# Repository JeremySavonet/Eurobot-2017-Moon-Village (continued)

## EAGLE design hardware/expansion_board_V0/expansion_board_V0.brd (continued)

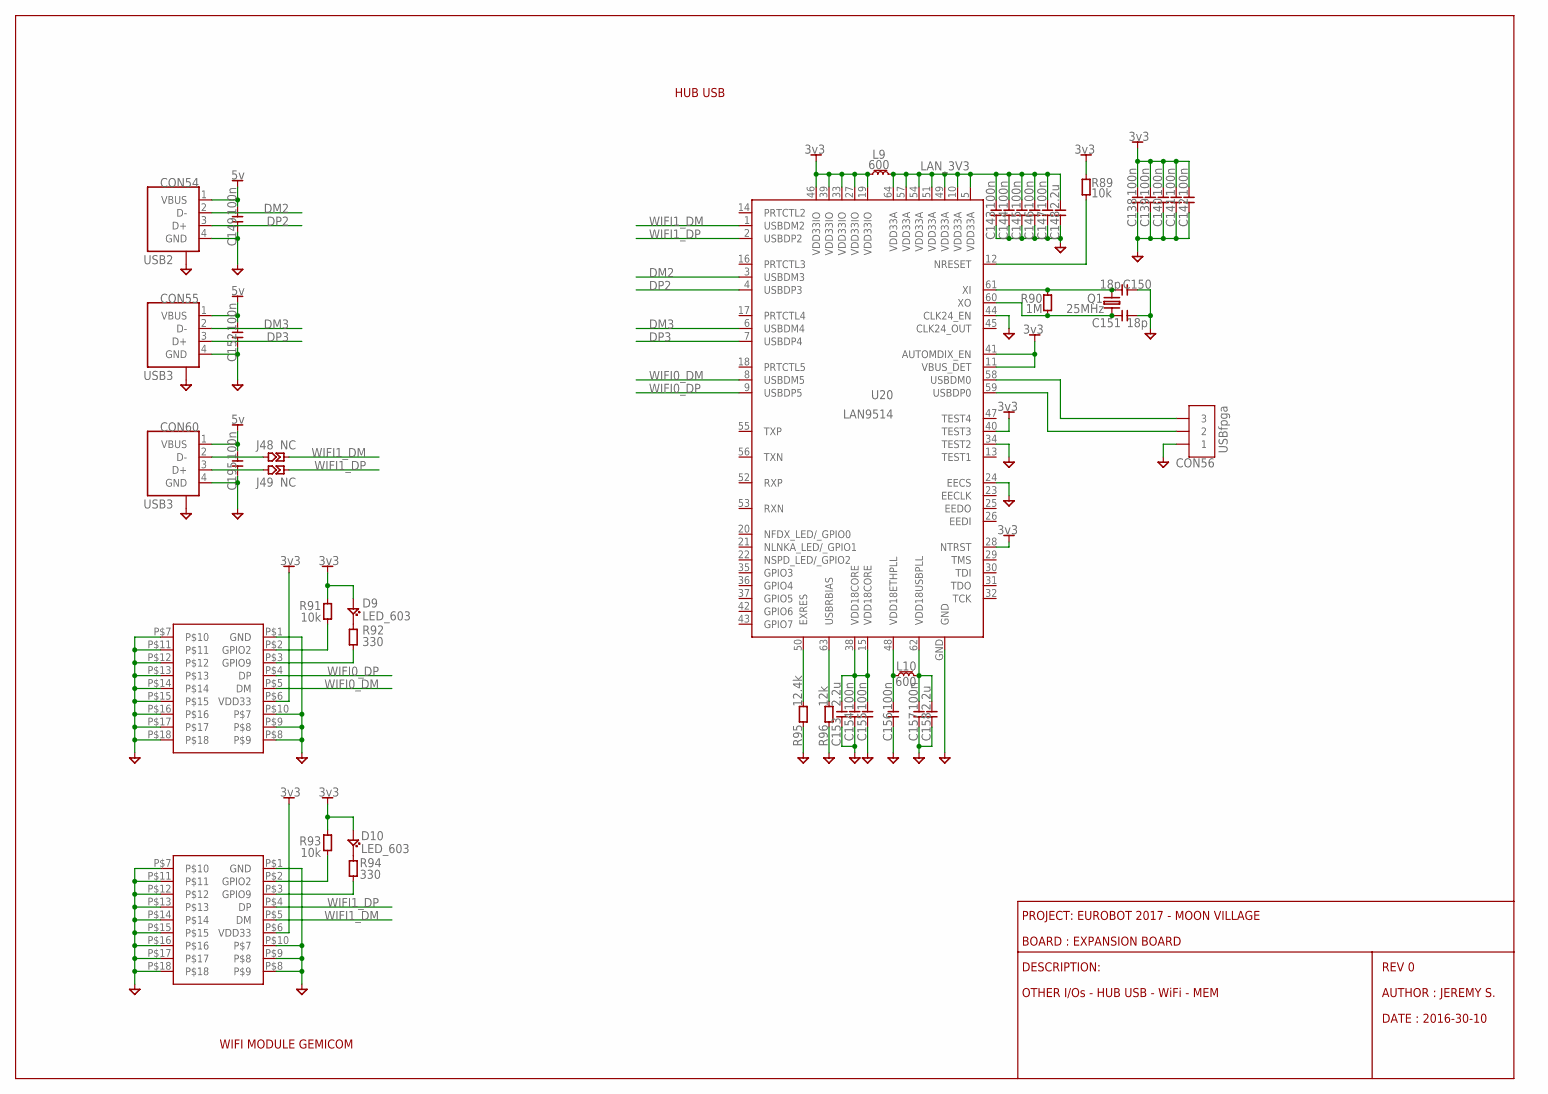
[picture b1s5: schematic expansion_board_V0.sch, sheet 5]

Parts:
C138, C139, C140, C141, C142, C143, C144, C145, C146, C147, C149, C152, C154, C155, C156, C157, C195: 100n; CAPC1005X55N
C148, C153, C158: 2.2u; CAPC1608X95N
C150, C151: 18p; CAPC1005X55N
CON54: USB2; USB_A
CON55, CON60: USB3; USB_A
CON56: USBfpga; CON254P762X400-3N-S
D9, D10: LED_603; LEDC1608X60N
J48, J49: NC; JUMC1005X50N
L9, L10: 600; INDC1608X95N
Q1: 25MHz; XTAL500X320X130N
R89, R91, R93: 10k; RESC1005X40N
R90: 1M; RESC1005X40N
R92, R94: 330; RESC1005X40N
R95: 12.4k; RESC1005X40N
R96: 12k; RESC1005X40N
U20: LAN9514; QFN50P900X900X100-65N
U21, U22: LGA22U

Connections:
3V3: C138.2, C139.2, C140.2, C141.2, C142.2, D9.A, D10.A, L9.1, R89.2, R91.2, R93.2, U20.11 (VBUS_DET), U20.19 (VDD33IO), U20.27 (VDD33IO), U20.28 (NTRST), U20.33 (VDD33IO), U20.39 (VDD33IO), U20.40 (TEST3), U20.41 (AUTOMDIX_EN), U20.46 (VDD33IO), U21.P$6 (VDD33), U22.P$6 (VDD33); also elsewhere on the board
5V: C149.2, C152.2, C195.2, CON54.1 (VBUS), CON55.1 (VBUS), CON60.1 (VBUS); also elsewhere on the board
DM2: CON54.2 (D-), U20.3 (USBDM3)
DM3: CON55.2 (D-), U20.6 (USBDM4)
DP2: CON54.3 (D+), U20.4 (USBDP3)
DP3: CON55.3 (D+), U20.7 (USBDP4)
GND: C138.1, C139.1, C140.1, C141.1, C142.1, C143.1, C144.1, C145.1, C146.1, C147.1, C148.P$1, C149.1, C150.1, C151.1, C152.1, C153.P$1, C154.1, C155.1, C156.1, C157.1, C158.P$1, C195.1, CON54.4 (GND), CON54.GND1 (GND), CON54.GND2 (GND), CON55.4 (GND), CON55.GND1 (GND), CON55.GND2 (GND), CON56.1, CON60.4 (GND), CON60.GND1 (GND), CON60.GND2 (GND), R95.1, R96.1, U20.24 (EECS), U20.34 (TEST2), U20.44 (CLK24_EN), U20.GND, U21.P$1 (GND), U21.P$7, U21.P$8, U21.P$9, U21.P$10, U21.P$11, U21.P$12, U21.P$13, U21.P$14, U21.P$15, U21.P$16, U21.P$17, U21.P$18, U22.P$1 (GND), U22.P$7, U22.P$8, U22.P$9, U22.P$10, U22.P$11, U22.P$12, U22.P$13, U22.P$14, U22.P$15, U22.P$16, U22.P$17, U22.P$18; also elsewhere on the board
LAN_3V3: C143.2, C144.2, C145.2, C146.2, C147.2, C148.P$2, L9.2, U20.5 (VDD33A), U20.10 (VDD33A), U20.49 (VDD33A), U20.51 (VDD33A), U20.54 (VDD33A), U20.57 (VDD33A), U20.64 (VDD33A)
unnamed: CON60.2 (D-), J48.P$1 (1)
unnamed: CON60.3 (D+), J49.P$1 (1)
unnamed: D10.C, R94.2
unnamed: D9.C, R92.2
unnamed: C157.2, C158.P$2, L10.2, U20.62 (VDD18USBPLL)
unnamed: C153.P$2, C154.2, C155.2, U20.15 (VDD18CORE), U20.38 (VDD18CORE)
unnamed: C156.2, L10.1, U20.48 (VDD18ETHPLL)
unnamed: R95.2, U20.50 (EXRES)
unnamed: R96.2, U20.63 (USBRBIAS)
unnamed: C151.2, Q1.2, R90.1, U20.60 (XO)
unnamed: CON56.2, U20.59 (USBDP0)
unnamed: CON56.3, U20.58 (USBDM0)
unnamed: R89.1, U20.12 (NRESET)
unnamed: C150.2, Q1.1, R90.2, U20.61 (XI)
WIFI0_DM: U20.8 (USBDM5), U21.P$5 (DM)
WIFI0_DP: U20.9 (USBDP5), U21.P$4 (DP)
WIFI1_DM: J48.P$2 (2), U20.1 (USBDM2), U22.P$5 (DM)
WIFI1_DP: J49.P$2 (2), U20.2 (USBDP2), U22.P$4 (DP)
WIFI1_LED: R94.1, U22.P$3 (GPIO9)
WIFI1_LED1: R92.1, U21.P$3 (GPIO9)
WIFI1_WPS: R93.1, U22.P$2 (GPIO2)
WIFI1_WPS1: R91.1, U21.P$2 (GPIO2)

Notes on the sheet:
REV 0
AUTHOR : JEREMY S.
DATE : 2016-30-10
DESCRIPTION:
BOARD : EXPANSION BOARD
PROJECT: EUROBOT 2017 - MOON VILLAGE
OTHER I/Os - HUB USB - WiFi - MEM
HUB USB
WIFI MODULE GEMICOM

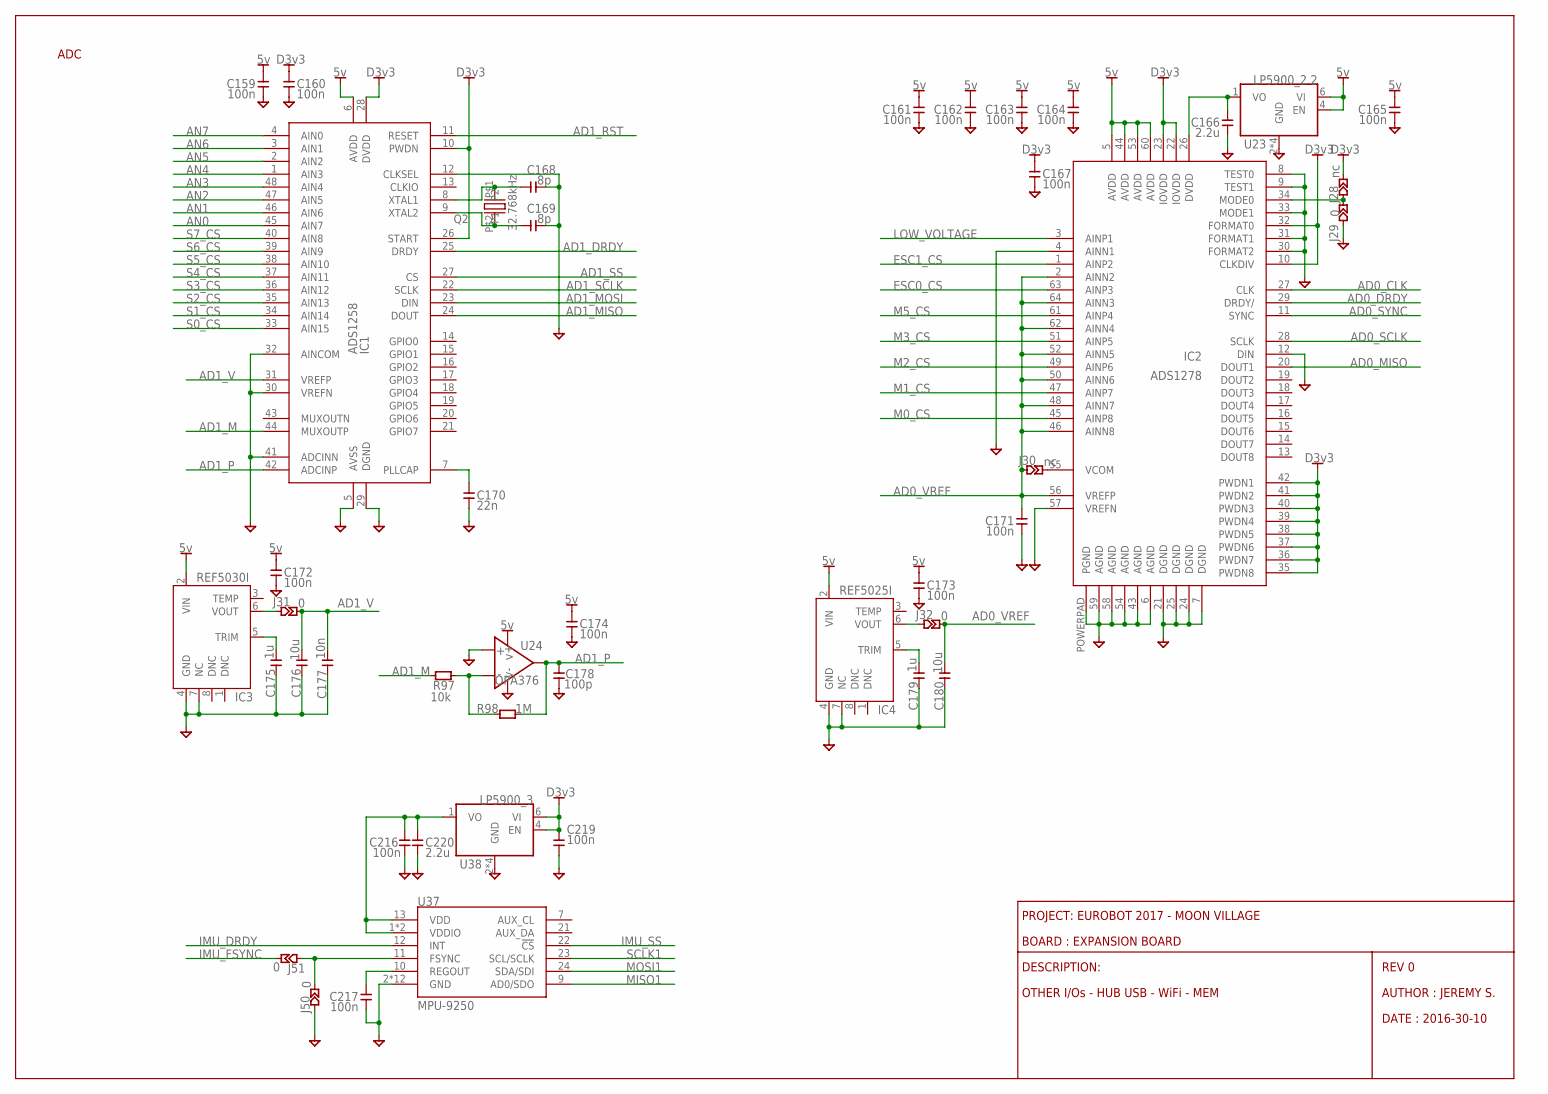
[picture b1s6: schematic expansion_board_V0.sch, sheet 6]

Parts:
C159, C160, C161, C162, C163, C164, C165, C167, C171, C172, C173, C174, C216, C217, C219: 100n; CAPC1005X55N
C166, C220: 2.2u; CAPC1608X95N
C168, C169: 8p; CAPC1005X55N
C170: 22n; CAPC1005X55N
C175, C179: 1u; CAPC1608X95N
C176, C180: 10u; CAPC2013X100N
C177: 10n; CAPC1005X55N
C178: 100p; CAPC1005X55N
IC1: ADS1258; QFN48
IC2: ADS1278; TQFP64_POWERPAD
IC3: REF5030I; MSOP8_0.65
IC4: REF5025I; MSOP8_0.65
J28, J30: nc; JUMC1005X50N
J29, J31, J32, J50, J51: 0; JUMC1005X50N
Q2: 32.768kHz; 1206
R97: 10k; RESC1005X40N
R98: 1M; RESC1005X40N
U23: LP5900_2.2; SON65P250X220X80-7N
U24: OPA376; SC70-5N
U37: MPU-9250; QFN24-3X3
U38: LP5900_3; SON65P250X220X80-7N

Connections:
5V: C159.2, C161.2, C162.2, C163.2, C164.2, C165.2, C172.2, C173.2, C174.2, IC1.6 (AVDD), IC2.5 (AVDD), IC2.44 (AVDD), IC2.53 (AVDD), IC2.60 (AVDD), IC3.2 (VIN), IC4.2 (VIN), U23.4 (EN), U23.6 (VI), U24.P$5 (VCC); also elsewhere on the board
AD0_CLK: IC2.27 (CLK); also elsewhere on the board
AD0_DRDY: IC2.29 (DRDY/); also elsewhere on the board
AD0_MISO: IC2.20 (DOUT1); also elsewhere on the board
AD0_SCLK: IC2.28 (SCLK); also elsewhere on the board
AD0_SYNC: IC2.11 (SYNC); also elsewhere on the board
AD0_VREF: C171.2, C180.P$1, IC2.2 (AINN2), IC2.46 (AINN8), IC2.48 (AINN7), IC2.50 (AINN6), IC2.52 (AINN5), IC2.56 (VREFP), IC2.62 (AINN4), IC2.64 (AINN3), J30.P$1 (1), J32.P$2 (2); also elsewhere on the board
AD1_DRDY: IC1.25 (DRDY); also elsewhere on the board
AD1_M: IC1.44 (MUXOUTP), R97.1
AD1_MISO: IC1.24 (DOUT); also elsewhere on the board
AD1_MOSI: IC1.23 (DIN); also elsewhere on the board
AD1_P: C178.2, IC1.42 (ADCINP), R98.2, U24.P$4 (OUT)
AD1_RST: IC1.11 (RESET); also elsewhere on the board
AD1_SCLK: IC1.22 (SCLK); also elsewhere on the board
AD1_SS: IC1.27 (CS); also elsewhere on the board
AD1_V: C176.P$1, C177.2, IC1.31 (VREFP), J31.P$2 (2)
AN0: IC1.45 (AIN7); also elsewhere on the board
AN1: IC1.46 (AIN6); also elsewhere on the board
AN2: IC1.47 (AIN5); also elsewhere on the board
AN3: IC1.48 (AIN4); also elsewhere on the board
AN4: IC1.1 (AIN3); also elsewhere on the board
AN5: IC1.2 (AIN2); also elsewhere on the board
AN6: IC1.3 (AIN1); also elsewhere on the board
AN7: IC1.4 (AIN0); also elsewhere on the board
D3V3: C160.2, C167.2, C219.2, IC1.10 (PWDN), IC1.26 (START), IC1.28 (DVDD), IC2.10 (CLKDIV), IC2.22 (IOVDD), IC2.23 (IOVDD), IC2.32 (FORMAT0), IC2.35 (PWDN8), IC2.36 (PWDN7), IC2.37 (PWDN6), IC2.38 (PWDN5), IC2.39 (PWDN4), IC2.40 (PWDN3), IC2.41 (PWDN2), IC2.42 (PWDN1), J28.P$2 (2), U38.4 (EN), U38.6 (VI); also elsewhere on the board
ESC0_CS: IC2.63 (AINP3); also elsewhere on the board
ESC1_CS: IC2.1 (AINP2); also elsewhere on the board
GND: C159.1, C160.1, C161.1, C162.1, C163.1, C164.1, C165.1, C166.P$1, C167.1, C168.1, C169.1, C170.1, C171.1, C172.1, C173.1, C174.1, C175.P$2, C176.P$2, C177.1, C178.1, C179.P$2, C180.P$2, C216.1, C217.1, C219.1, C220.P$1, IC1.5 (AVSS), IC1.12 (CLKSEL), IC1.29 (DGND), IC1.30 (VREFN), IC1.32 (AINCOM), IC1.41 (ADCINN), IC2.4 (AINN1), IC2.6 (AGND), IC2.7 (DGND), IC2.8 (TEST0), IC2.9 (TEST1), IC2.12 (DIN), IC2.21 (DGND), IC2.24 (DGND), IC2.25 (DGND), IC2.30 (FORMAT2), IC2.31 (FORMAT1), IC2.33 (MODE1), IC2.43 (AGND), IC2.54 (AGND), IC2.57 (VREFN), IC2.58 (AGND), IC2.59 (AGND), IC2.POWERPAD (PGND), IC3.4 (GND), IC3.7 (NC), IC4.4 (GND), IC4.7 (NC), J29.P$1 (1), J50.P$1 (1), U23.2 (GND), U23.3 (GND), U23.5 (GND), U23.GND, U24.P$1 (+), U24.P$2 (GND), U37.2 (GND), U37.3 (GND), U37.4 (GND), U37.5 (GND), U37.6 (GND), U37.14 (GND), U37.15 (GND), U37.16 (GND), U37.17 (GND), U37.18 (GND), U37.20 (GND), U37.PAD (GND), U38.2 (GND), U38.3 (GND), U38.5 (GND), U38.GND; also elsewhere on the board
IMU_DRDY: U37.12 (INT); also elsewhere on the board
IMU_FSYNC: J51.P$2 (2); also elsewhere on the board
IMU_SS: U37.22 (!CS); also elsewhere on the board
LOW_VOLTAGE: IC2.3 (AINP1); also elsewhere on the board
M0_CS: IC2.45 (AINP8); also elsewhere on the board
M1_CS: IC2.47 (AINP7); also elsewhere on the board
M2_CS: IC2.49 (AINP6); also elsewhere on the board
M3_CS: IC2.51 (AINP5); also elsewhere on the board
M5_CS: IC2.61 (AINP4); also elsewhere on the board
MISO1: U37.9 (AD0/SDO); also elsewhere on the board
MOSI1: U37.24 (SDA/SDI); also elsewhere on the board
unnamed: R97.2, R98.1, U24.P$3 (-)
unnamed: C168.2, IC1.8 (XTAL1), Q2.P$1 (P1)
unnamed: C175.P$1, IC3.5 (TRIM)
unnamed: IC3.6 (VOUT), J31.P$1 (1)
unnamed: C170.2, IC1.7 (PLLCAP)
unnamed: C169.2, IC1.9 (XTAL2), Q2.P$2 (P2)
unnamed: C216.2, C220.P$2, U37.1 (VDDIO), U37.8 (VDDIO), U37.13 (VDD), U38.1 (VO)
unnamed: J50.P$2 (2), J51.P$1 (1), U37.11 (FSYNC)
unnamed: IC2.55 (VCOM), J30.P$2 (2)
unnamed: IC2.34 (MODE0), J28.P$1 (1), J29.P$2 (2)
unnamed: C179.P$1, IC4.5 (TRIM)
unnamed: C166.P$2, IC2.26 (DVDD), U23.1 (VO)
unnamed: IC4.6 (VOUT), J32.P$1 (1)
REGOUT1: C217.2, U37.10 (REGOUT)
S0_CS: IC1.33 (AIN15); also elsewhere on the board
S1_CS: IC1.34 (AIN14); also elsewhere on the board
S2_CS: IC1.35 (AIN13); also elsewhere on the board
S3_CS: IC1.36 (AIN12); also elsewhere on the board
S4_CS: IC1.37 (AIN11); also elsewhere on the board
S5_CS: IC1.38 (AIN10); also elsewhere on the board
S6_CS: IC1.39 (AIN9); also elsewhere on the board
S7_CS: IC1.40 (AIN8); also elsewhere on the board
SCLK1: U37.23 (SCL/SCLK); also elsewhere on the board

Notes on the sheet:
ADC
REV 0
AUTHOR : JEREMY S.
DATE : 2016-30-10
DESCRIPTION:
BOARD : EXPANSION BOARD
PROJECT: EUROBOT 2017 - MOON VILLAGE
OTHER I/Os - HUB USB - WiFi - MEM

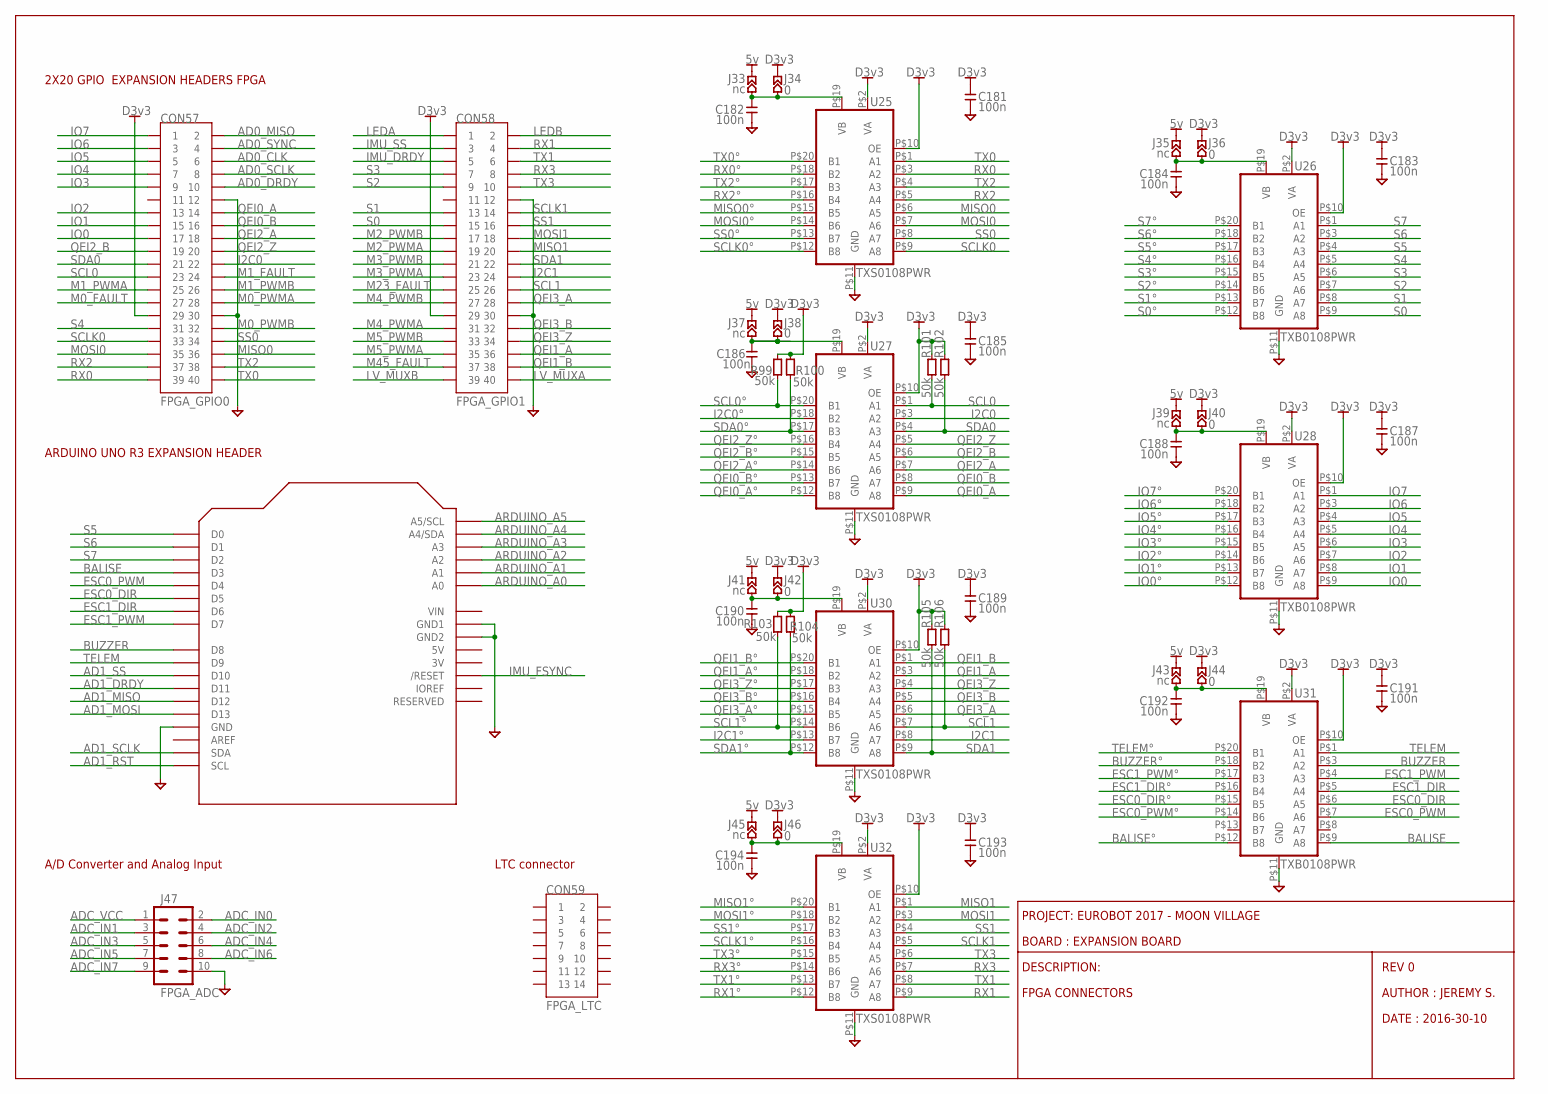
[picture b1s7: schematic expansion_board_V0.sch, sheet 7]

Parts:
C181, C182, C183, C184, C185, C186, C187, C188, C189, C190, C191, C192, C193, C194: 100n; CAPC1005X55N
CON57: FPGA_GPIO0; CON254P5080X600-40N
CON58: FPGA_GPIO1; CON254P5080X600-40N
CON59: FPGA_LTC; CON200P1700X400-2X7N
J33, J35, J37, J39, J41, J43, J45: nc; JUMC1005X50N
J34, J36, J38, J40, J42, J44, J46: 0; JUMC1005X50N
J47: FPGA_ADC; 2X5_NOSILK
R99, R100, R101, R102, R103, R104, R105, R106: 50k; RESC1005X40N
U25, U27, U30, U32: TXS0108PWR; SOP65P640X110-20N
U26, U28, U31: TXB0108PWR; SOP65P640X110-20N
U29: FPGA_ARDUINO; ARDUINOR3

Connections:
5V: J33.P$2 (2), J35.P$2 (2), J37.P$2 (2), J39.P$2 (2), J41.P$2 (2), J43.P$2 (2), J45.P$2 (2); also elsewhere on the board
AD0_CLK: CON57.6; also elsewhere on the board
AD0_DRDY: CON57.10; also elsewhere on the board
AD0_MISO: CON57.2; also elsewhere on the board
AD0_SCLK: CON57.8; also elsewhere on the board
AD0_SYNC: CON57.4; also elsewhere on the board
AD1_DRDY: U29.D11; also elsewhere on the board
AD1_MISO: U29.D12; also elsewhere on the board
AD1_MOSI: U29.D13; also elsewhere on the board
AD1_RST: U29.SCL; also elsewhere on the board
AD1_SCLK: U29.SDA; also elsewhere on the board
AD1_SS: U29.D10; also elsewhere on the board
ADC_IN0: J47.2
ADC_IN1: J47.3
ADC_IN2: J47.4
ADC_IN3: J47.5
ADC_IN4: J47.6
ADC_IN5: J47.7
ADC_IN6: J47.8
ADC_IN7: J47.9
ADC_VCC: J47.1
ARDUINO_A0: U29.A0
ARDUINO_A1: U29.A1
ARDUINO_A2: U29.A2
ARDUINO_A3: U29.A3
ARDUINO_A4: U29.A4 (A4/SDA)
ARDUINO_A5: U29.A5 (A5/SCL)
BALISE: U29.D3, U31.P$9 (A8)
BALISE°: U31.P$12 (B8); also elsewhere on the board
BUZZER: U29.D8, U31.P$3 (A2)
BUZZER°: U31.P$18 (B2); also elsewhere on the board
D3V3: C181.2, C183.2, C185.2, C187.2, C189.2, C191.2, C193.2, CON57.29, CON58.29, J34.P$2 (2), J36.P$2 (2), J38.P$2 (2), J40.P$2 (2), J42.P$2 (2), J44.P$2 (2), J46.P$2 (2), R99.2, R100.2, R101.2, R102.2, R103.2, R104.2, R105.2, R106.2, U25.P$2 (VA), U25.P$10 (OE), U26.P$2 (VA), U26.P$10 (OE), U27.P$2 (VA), U27.P$10 (OE), U28.P$2 (VA), U28.P$10 (OE), U30.P$2 (VA), U30.P$10 (OE), U31.P$2 (VA), U31.P$10 (OE), U32.P$2 (VA), U32.P$10 (OE); also elsewhere on the board
ESC0_DIR: U29.D5, U31.P$6 (A5)
ESC0_DIR°: U31.P$15 (B5); also elsewhere on the board
ESC0_PWM: U29.D4, U31.P$7 (A6)
ESC0_PWM°: U31.P$14 (B6); also elsewhere on the board
ESC1_DIR: U29.D6, U31.P$5 (A4)
ESC1_DIR°: U31.P$16 (B4); also elsewhere on the board
ESC1_PWM: U29.D7, U31.P$4 (A3)
ESC1_PWM°: U31.P$17 (B3); also elsewhere on the board
GND: C181.1, C182.1, C183.1, C184.1, C185.1, C186.1, C187.1, C188.1, C189.1, C190.1, C191.1, C192.1, C193.1, C194.1, CON57.12, CON57.30, CON58.12, CON58.30, J47.10, U25.P$11 (GND), U26.P$11 (GND), U27.P$11 (GND), U28.P$11 (GND), U29.GND, U29.GND1, U29.GND2, U30.P$11 (GND), U31.P$11 (GND), U32.P$11 (GND); also elsewhere on the board
I2C0: CON57.22, U27.P$3 (A2)
I2C0°: U27.P$18 (B2); also elsewhere on the board
I2C1: CON58.24, U30.P$8 (A7)
I2C1°: U30.P$13 (B7); also elsewhere on the board
IMU_DRDY: CON58.5; also elsewhere on the board
IMU_FSYNC: U29.RESET (/RESET); also elsewhere on the board
IMU_SS: CON58.3; also elsewhere on the board
IO0: CON57.17, U28.P$9 (A8)
IO0°: U28.P$12 (B8); also elsewhere on the board
IO1: CON57.15, U28.P$8 (A7)
IO1°: U28.P$13 (B7); also elsewhere on the board
IO2: CON57.13, U28.P$7 (A6)
IO2°: U28.P$14 (B6); also elsewhere on the board
IO3: CON57.9, U28.P$6 (A5)
IO3°: U28.P$15 (B5); also elsewhere on the board
IO4: CON57.7, U28.P$5 (A4)
IO4°: U28.P$16 (B4); also elsewhere on the board
IO5: CON57.5, U28.P$4 (A3)
IO5°: U28.P$17 (B3); also elsewhere on the board
IO6: CON57.3, U28.P$3 (A2)
IO6°: U28.P$18 (B2); also elsewhere on the board
IO7: CON57.1, U28.P$1 (A1)
IO7°: U28.P$20 (B1); also elsewhere on the board
LEDA: CON58.1; also elsewhere on the board
LEDB: CON58.2; also elsewhere on the board
LV_MUXA: CON58.40; also elsewhere on the board
LV_MUXB: CON58.39; also elsewhere on the board
M0_FAULT: CON57.27; also elsewhere on the board
M0_PWMA: CON57.28; also elsewhere on the board
M0_PWMB: CON57.32; also elsewhere on the board
M1_FAULT: CON57.24; also elsewhere on the board
M1_PWMA: CON57.25; also elsewhere on the board
M1_PWMB: CON57.26; also elsewhere on the board
M2_PWMA: CON58.19; also elsewhere on the board
M2_PWMB: CON58.17; also elsewhere on the board
M3_PWMA: CON58.23; also elsewhere on the board
M3_PWMB: CON58.21; also elsewhere on the board
M4_PWMA: CON58.31; also elsewhere on the board
M4_PWMB: CON58.27; also elsewhere on the board
M5_PWMA: CON58.35; also elsewhere on the board
M5_PWMB: CON58.33; also elsewhere on the board
M23_FAULT: CON58.25; also elsewhere on the board
M45_FAULT: CON58.37; also elsewhere on the board
MISO0: CON57.36, U25.P$6 (A5)
MISO0°: U25.P$15 (B5); also elsewhere on the board
MISO1: CON58.20, U32.P$1 (A1); also elsewhere on the board
MISO1°: U32.P$20 (B1); also elsewhere on the board
MOSI0: CON57.35, U25.P$7 (A6)
MOSI0°: U25.P$14 (B6); also elsewhere on the board
MOSI1: CON58.18, U32.P$3 (A2); also elsewhere on the board
MOSI1°: U32.P$18 (B2); also elsewhere on the board
unnamed: C182.2, J33.P$1 (1), J34.P$1 (1), U25.P$19 (VB)
unnamed: C186.2, J37.P$1 (1), J38.P$1 (1), U27.P$19 (VB)
unnamed: C190.2, J41.P$1 (1), J42.P$1 (1), U30.P$19 (VB)
unnamed: C194.2, J45.P$1 (1), J46.P$1 (1), U32.P$19 (VB)
unnamed: C184.2, J35.P$1 (1), J36.P$1 (1), U26.P$19 (VB)
unnamed: C188.2, J39.P$1 (1), J40.P$1 (1), U28.P$19 (VB)
unnamed: C192.2, J43.P$1 (1), J44.P$1 (1), U31.P$19 (VB)
QEI0_A: CON57.14, U27.P$9 (A8)
QEI0_A°: U27.P$12 (B8); also elsewhere on the board
QEI0_B: CON57.16, U27.P$8 (A7)
QEI0_B°: U27.P$13 (B7); also elsewhere on the board
QEI1_A: CON58.36, U30.P$3 (A2)
QEI1_A°: U30.P$18 (B2); also elsewhere on the board
QEI1_B: CON58.38, U30.P$1 (A1)
QEI1_B°: U30.P$20 (B1); also elsewhere on the board
QEI2_A: CON57.18, U27.P$7 (A6)
QEI2_A°: U27.P$14 (B6); also elsewhere on the board
QEI2_B: CON57.19, U27.P$6 (A5)
QEI2_B°: U27.P$15 (B5); also elsewhere on the board
QEI2_Z: CON57.20, U27.P$5 (A4)
QEI2_Z°: U27.P$16 (B4); also elsewhere on the board
QEI3_A: CON58.28, U30.P$6 (A5)
QEI3_A°: U30.P$15 (B5); also elsewhere on the board
QEI3_B: CON58.32, U30.P$5 (A4)
QEI3_B°: U30.P$16 (B4); also elsewhere on the board
QEI3_Z: CON58.34, U30.P$4 (A3)
QEI3_Z°: U30.P$17 (B3); also elsewhere on the board
RX0: CON57.39, U25.P$3 (A2)
RX0°: U25.P$18 (B2); also elsewhere on the board
RX1: CON58.4, U32.P$9 (A8)
RX1°: U32.P$12 (B8); also elsewhere on the board
RX2: CON57.37, U25.P$5 (A4)
RX2°: U25.P$16 (B4); also elsewhere on the board
RX3: CON58.8, U32.P$7 (A6)
RX3°: U32.P$14 (B6); also elsewhere on the board
S0: CON58.15, U26.P$9 (A8)
S0°: U26.P$12 (B8); also elsewhere on the board
S1: CON58.13, U26.P$8 (A7)
S1°: U26.P$13 (B7); also elsewhere on the board
S2: CON58.9, U26.P$7 (A6)
S2°: U26.P$14 (B6); also elsewhere on the board
S3: CON58.7, U26.P$6 (A5)
S3°: U26.P$15 (B5); also elsewhere on the board
S4: CON57.31, U26.P$5 (A4)
S4°: U26.P$16 (B4); also elsewhere on the board
S5: U26.P$4 (A3), U29.D0
S5°: U26.P$17 (B3); also elsewhere on the board
S6: U26.P$3 (A2), U29.D1
S6°: U26.P$18 (B2); also elsewhere on the board
S7: U26.P$1 (A1), U29.D2
S7°: U26.P$20 (B1); also elsewhere on the board
SCL0: CON57.23, R101.1, U27.P$1 (A1)
SCL0°: R99.1, U27.P$20 (B1); also elsewhere on the board
SCL1: CON58.26, R106.1, U30.P$7 (A6)
SCL1°: R103.1, U30.P$14 (B6); also elsewhere on the board
SCLK0: CON57.33, U25.P$9 (A8)
SCLK0°: U25.P$12 (B8); also elsewhere on the board
SCLK1: CON58.14, U32.P$5 (A4); also elsewhere on the board
SCLK1°: U32.P$16 (B4); also elsewhere on the board
SDA0: CON57.21, R102.1, U27.P$4 (A3)
SDA0°: R100.1, U27.P$17 (B3); also elsewhere on the board
SDA1: CON58.22, R105.1, U30.P$9 (A8)
SDA1°: R104.1, U30.P$12 (B8); also elsewhere on the board
SS0: CON57.34, U25.P$8 (A7)
SS0°: U25.P$13 (B7); also elsewhere on the board
SS1: CON58.16, U32.P$4 (A3)
SS1°: U32.P$17 (B3); also elsewhere on the board
TELEM: U29.D9, U31.P$1 (A1)
TELEM°: U31.P$20 (B1); also elsewhere on the board
TX0: CON57.40, U25.P$1 (A1)
TX0°: U25.P$20 (B1); also elsewhere on the board
TX1: CON58.6, U32.P$8 (A7)
TX1°: U32.P$13 (B7); also elsewhere on the board
TX2: CON57.38, U25.P$4 (A3)
TX2°: U25.P$17 (B3); also elsewhere on the board
TX3: CON58.10, U32.P$6 (A5)
TX3°: U32.P$15 (B5); also elsewhere on the board

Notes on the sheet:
REV 0
AUTHOR : JEREMY S.
DATE : 2016-30-10
DESCRIPTION:
BOARD : EXPANSION BOARD
PROJECT: EUROBOT 2017 - MOON VILLAGE
FPGA CONNECTORS
2X20 GPIO EXPANSION HEADERS FPGA
ARDUINO UNO R3 EXPANSION HEADER
A/D Converter and Analog Input
LTC connector

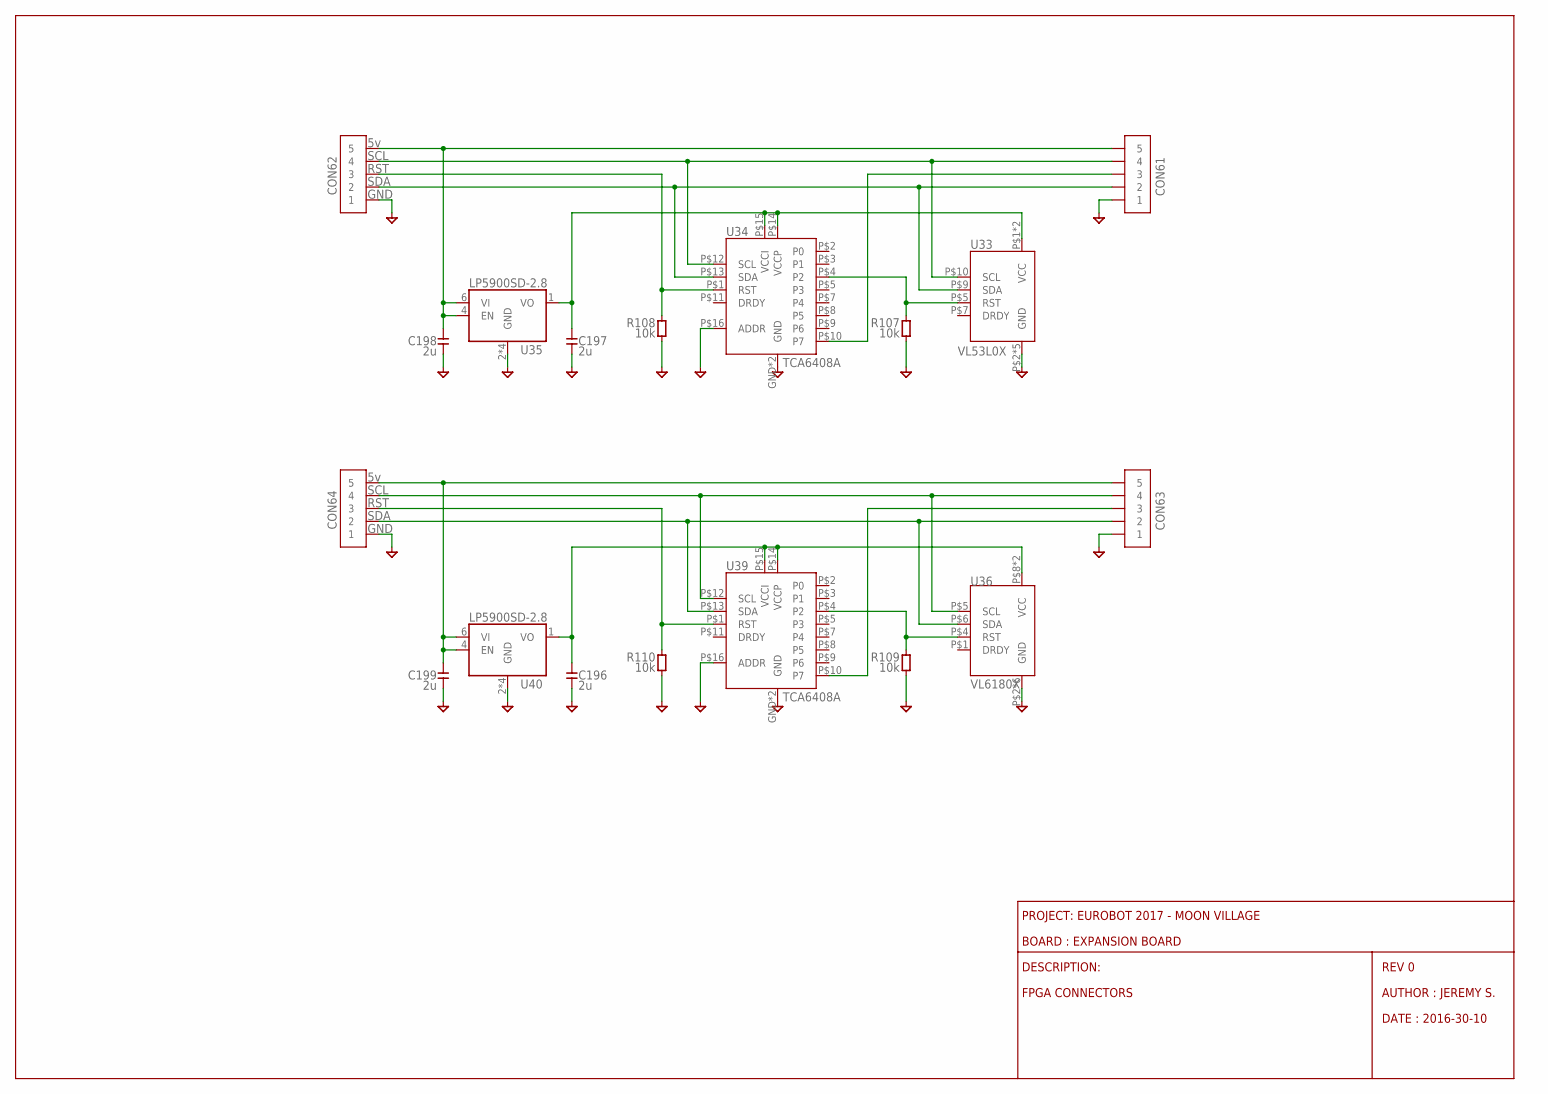
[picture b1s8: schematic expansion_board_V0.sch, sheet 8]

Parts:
C196, C197, C198, C199: 2u; CAPC1608X95N
CON61, CON62, CON63, CON64: CON5_2.54S; CON254P1270X400-5S
R107, R108, R109, R110: 10k; RESC1005X40N
U33: VL53L0X
U34, U39: TCA6408A; QFN50P300X300X80-17N
U35, U40: LP5900SD-2.8; SON65P250X220X80-7N
U36: VL6180X

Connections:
GND: C196.P$2, C197.P$2, C198.P$2, C199.P$2, CON61.1, CON62.1, CON63.1, CON64.1, R107.2, R108.2, R109.2, R110.2, U33.P$2 (GND), U33.P$3 (GND), U33.P$4 (GND), U33.P$6 (GND), U33.P$12 (GND), U34.GND, U34.P$6 (GND), U34.P$16 (ADDR), U35.2 (GND), U35.3 (GND), U35.5 (GND), U35.GND, U36.P$2 (GND), U36.P$3 (GND), U36.P$7 (GND), U36.P$9 (GND), U36.P$11 (GND), U36.P$12 (GND), U39.GND, U39.P$6 (GND), U39.P$16 (ADDR), U40.2 (GND), U40.3 (GND), U40.5 (GND), U40.GND; also elsewhere on the board
unnamed: R107.1, U33.P$5 (RST), U34.P$4 (P2)
unnamed: CON62.3, R108.1, U34.P$1 (RST)
unnamed: CON61.2, CON62.2, U33.P$9 (SDA), U34.P$13 (SDA)
unnamed: CON61.4, CON62.4, U33.P$10 (SCL), U34.P$12 (SCL)
unnamed: CON61.3, U34.P$10 (P7)
unnamed: C198.P$1, CON61.5, CON62.5, U35.4 (EN), U35.6 (VI)
unnamed: C197.P$1, U33.P$1 (VCC), U33.P$11 (VCC), U34.P$14 (VCCP), U34.P$15 (VCCI), U35.1 (VO)
unnamed: C199.P$1, CON63.5, CON64.5, U40.4 (EN), U40.6 (VI)
unnamed: CON63.4, CON64.4, U36.P$5 (SCL), U39.P$12 (SCL)
unnamed: CON63.2, CON64.2, U36.P$6 (SDA), U39.P$13 (SDA)
unnamed: C196.P$1, U36.P$8 (VCC), U36.P$10 (VCC), U39.P$14 (VCCP), U39.P$15 (VCCI), U40.1 (VO)
unnamed: CON64.3, R110.1, U39.P$1 (RST)
unnamed: CON63.3, U39.P$10 (P7)
unnamed: R109.1, U36.P$4 (RST), U39.P$4 (P2)

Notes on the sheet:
REV 0
AUTHOR : JEREMY S.
DATE : 2016-30-10
DESCRIPTION:
BOARD : EXPANSION BOARD
PROJECT: EUROBOT 2017 - MOON VILLAGE
FPGA CONNECTORS
SDA
RST
SCL
GND
